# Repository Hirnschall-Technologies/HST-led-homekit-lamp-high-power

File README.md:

# High Power LED Lamp (HomeKit enabled, dimmable)
I designed this LED lighting system as a replacement for old halogen R7S uplights.      
These lamps often use high power (400W) bulbs outputing (according to the manufacturer) around 8800 lumen. Meanwhile the only off the shelf LED uplights I could find output 2000 lumen while using around 25W. Furthermore, altough replacement cob LEDs for R7S sockets are available they are typically "20W". I tested several of them and they started at around 15W, after around one hour they only used 10W, they are not bright enough, and they started flickering from time to time.

Also, I dislike how modern LED uplights have to be replaced entirely if a fault with the LEDs or dirver circuit occurs.
Using a modular design, we can reduce waste and wast less power.

### Features
- [x] High power Cree XHP50.3 LEDs (efficient, high CRI 90+) 
- [x] Modular design (2, 4, or 6 LEDs) 
- [x] Dimmable
- [x] Up to 108W, approx 12000 lumen
- [x] Homekit enabled (uses esp8266)
- [x] Manual On/Off switch in addition to Homekit (I use a 433MHz remote)
- [x] Uses 12V to 48V
- [x] Temperature sensor on each LED daughter board
- [x] Each LED on a separate daughter board, thus each led can be raplaced easily
- [x] Open source (Arduino compatible)

### References
The most useful resource for this project was SDG Electronics long-lasting video series on designing an LED ring-light for his microscope using the slightly older Cree XHP50.2 LEDs, as well as his modular LED driver board series.

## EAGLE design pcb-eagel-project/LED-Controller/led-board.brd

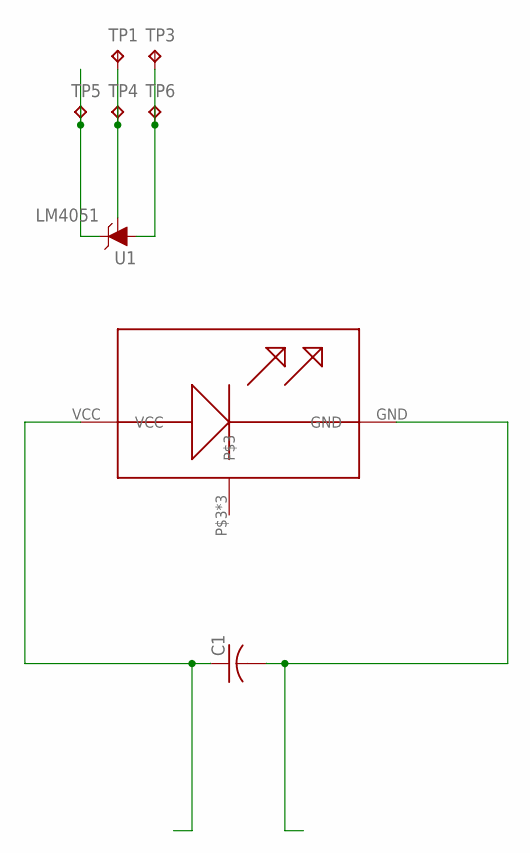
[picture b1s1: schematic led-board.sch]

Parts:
C1: C-USC0805; C0805
TP1, TP3, TP4, TP5, TP6: TPTP20SQ; TP20SQ
U1: LM4051; SOT23-3
U$3: XHP50.3

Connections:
unnamed: C1.1, U$3.VCC
unnamed: C1.2, U$3.GND
unnamed: TP1.TP, TP4.TP, U1.1 (ADJ)
unnamed: TP5.TP, U1.2 (C)
unnamed: TP3.TP, TP6.TP, U1.3 (A)

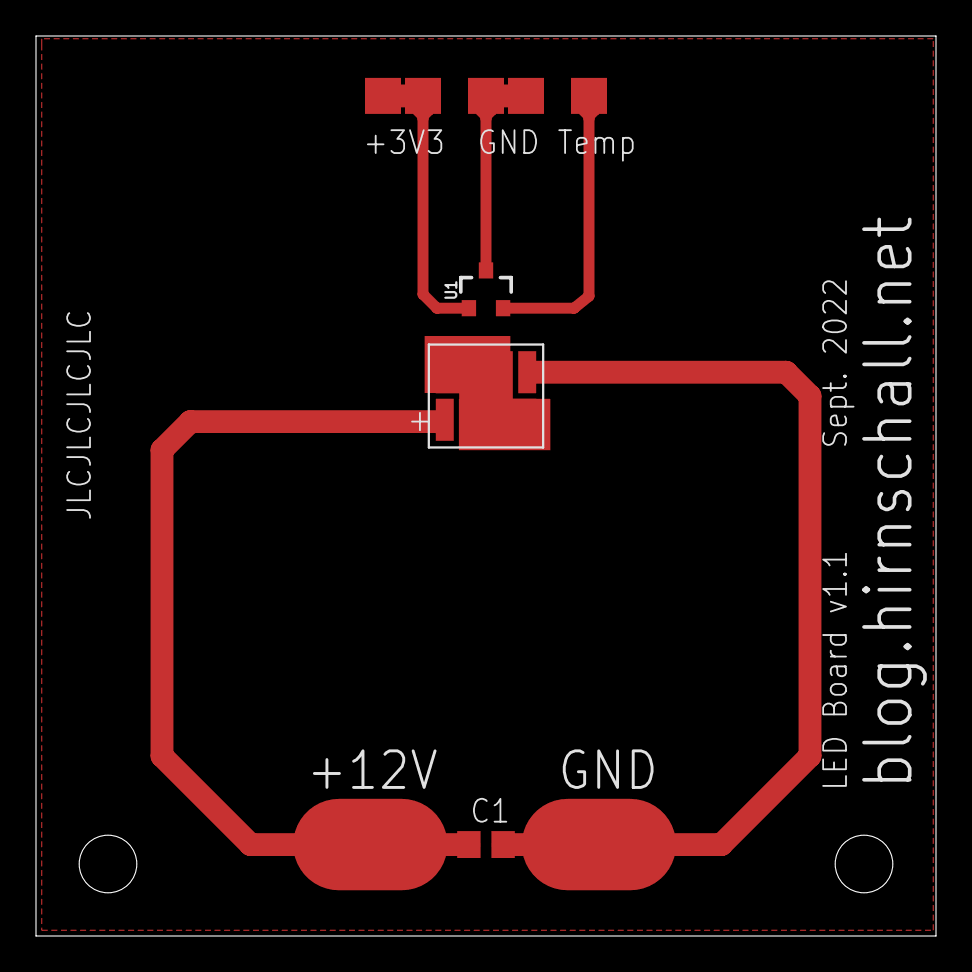
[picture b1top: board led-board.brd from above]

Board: 2 copper layers, 50.0 x 50.0 mm, 8 parts (0 on the bottom side), 5 nets.

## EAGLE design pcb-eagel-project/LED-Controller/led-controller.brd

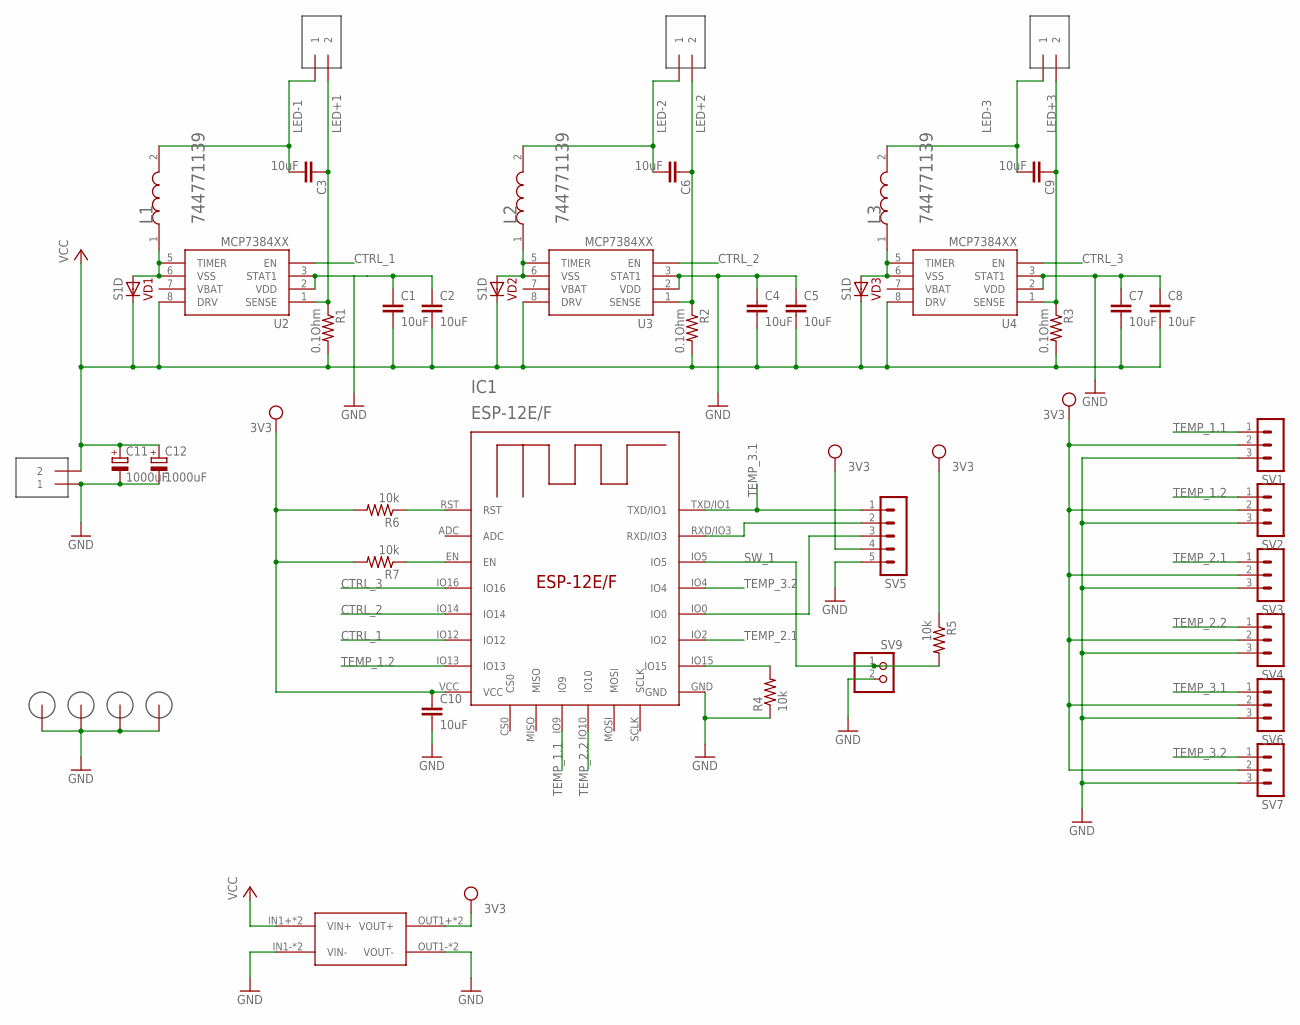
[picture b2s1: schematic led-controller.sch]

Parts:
C1, C2, C3, C4, C5, C6, C7, C8, C9, C10: 10uF; C0805K
C11, C12: 1000uF; E5-13
H1, H2, H3, H4: 3MM_HOLE
IC1: ESP-12E/F; ESP-12E
L1, L2, L3: 39uH; WURTH_ELECTRONICS_744771139_0
R1, R2, R3: 0.1Ohm; R1206
R4, R5, R6, R7: 10k; R0805
SV1, SV2, SV3, SV4, SV6, SV7: MA03-1
SV5: MA05-1
SV9: PINHD-1X2; 1X02
U2, U3, U4: MCP7384XX; MSOP8
U$3, U$5, U$7, U$8: TERMINAL_2P; KF301-2P
U$10: MP1584; DC-BRICK
VD1, VD2, VD3: S1D; DO214AC

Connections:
3V3: C10.1, IC1.VCC, R5.1, R6.2, R7.2, SV1.2, SV2.2, SV3.2, SV4.2, SV5.4, SV6.2, SV7.2, U$10.OUT1+ (VOUT+), U$10.OUT2+ (VOUT+)
CTRL_1: IC1.IO12, U2.4 (EN)
CTRL_2: IC1.IO14, U3.4 (EN)
CTRL_3: IC1.IO16, U4.4 (EN)
GND: C1.1, C2.1, C4.1, C5.1, C7.1, C8.1, C10.2, C11.-, C12.-, H1.P$1, H1.P$2, H1.P$3, H1.P$4, H1.P$5, H1.P$6, H1.P$7, H1.P$8, H1.P$9, H2.P$1, H2.P$2, H2.P$3, H2.P$4, H2.P$5, H2.P$6, H2.P$7, H2.P$8, H2.P$9, H3.P$1, H3.P$2, H3.P$3, H3.P$4, H3.P$5, H3.P$6, H3.P$7, H3.P$8, H3.P$9, H4.P$1, H4.P$2, H4.P$3, H4.P$4, H4.P$5, H4.P$6, H4.P$7, H4.P$8, H4.P$9, IC1.GND, R4.1, SV1.3, SV2.3, SV3.3, SV4.3, SV5.5, SV6.3, SV7.3, SV9.2, U2.2 (VDD), U2.3 (STAT1), U3.2 (VDD), U3.3 (STAT1), U4.2 (VDD), U4.3 (STAT1), U$8.1, U$10.IN1- (VIN-), U$10.IN2- (VIN-), U$10.OUT1- (VOUT-), U$10.OUT2- (VOUT-)
LED+1: C3.1, R1.1, U2.1 (SENSE), U$3.2
LED+2: C6.1, R2.1, U3.1 (SENSE), U$5.2
LED+3: C9.1, R3.1, U4.1 (SENSE), U$7.2
LED-1: C3.2, L1.2, U$3.1
LED-2: C6.2, L2.2, U$5.1
LED-3: C9.2, L3.2, U$7.1
unnamed: IC1.RST, R6.1
unnamed: IC1.EN, R7.1
unnamed: L2.1, U3.5 (TIMER), U3.6 (VSS), VD2.A
unnamed: L3.1, U4.5 (TIMER), U4.6 (VSS), VD3.A
unnamed: L1.1, U2.5 (TIMER), U2.6 (VSS), VD1.A
unnamed: IC1.IO15, R4.2
unnamed: IC1.IO0, SV5.3
unnamed: IC1.RXD/IO3, SV5.2
SW_1: IC1.IO5, R5.2, SV9.1
TEMP_1.1: IC1.IO9, SV1.1
TEMP_1.2: IC1.IO13, SV2.1
TEMP_2.1: IC1.IO2, SV3.1
TEMP_2.2: IC1.IO10, SV4.1
TEMP_3.1: IC1.TXD/IO1, SV5.1, SV6.1
TEMP_3.2: IC1.IO4, SV7.1
VCC: C1.2, C2.2, C4.2, C5.2, C7.2, C8.2, C11.+, C12.+, R1.2, R2.2, R3.2, U2.8 (DRV), U3.8 (DRV), U4.8 (DRV), U$8.2, U$10.IN1+ (VIN+), U$10.IN2+ (VIN+), VD1.C, VD2.C, VD3.C

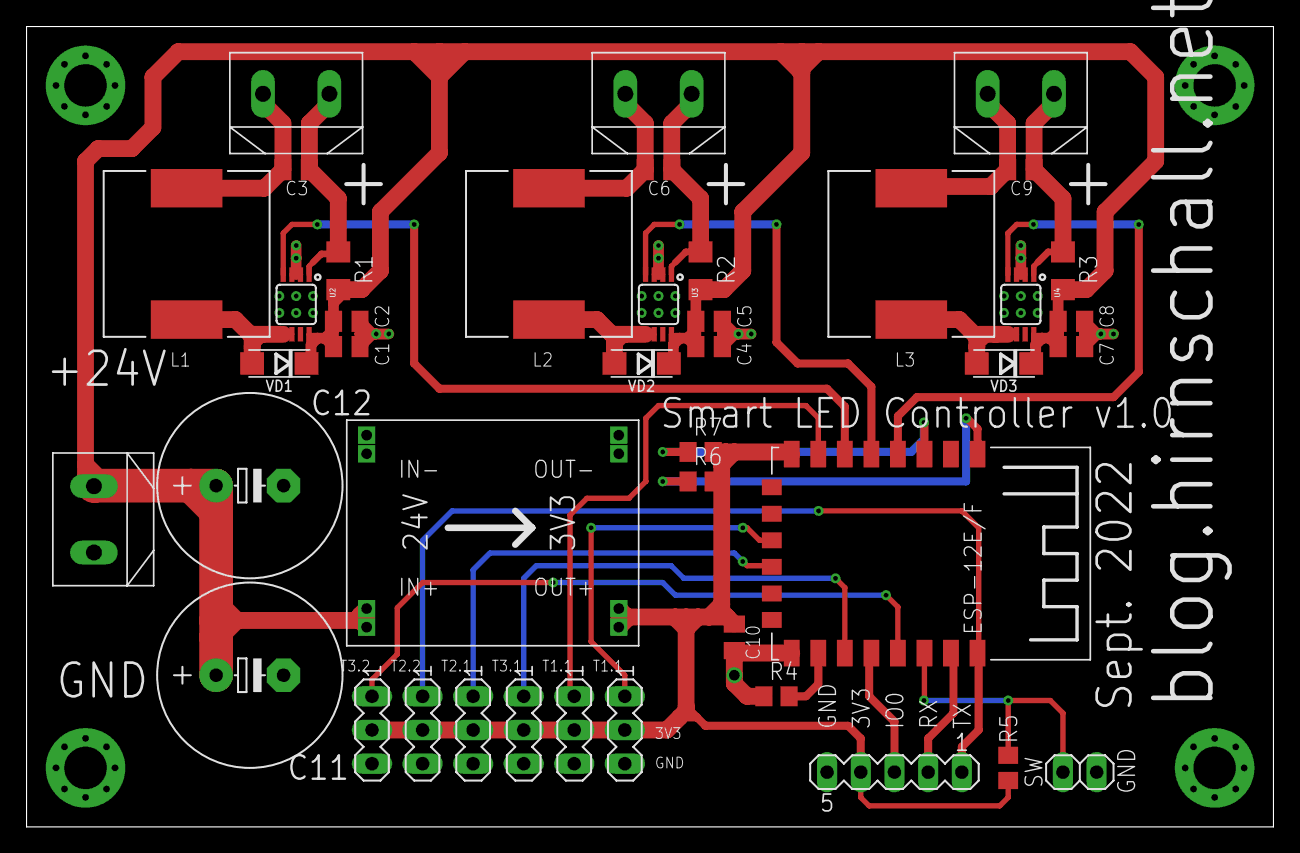
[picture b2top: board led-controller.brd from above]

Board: 2 copper layers, 94.0 x 60.3 mm, 46 parts (0 on the bottom side), 27 nets.

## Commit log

2022-10-09 first draft of an asymmetrical 6 led layout/mount for uplights
2022-10-10 add ed pcb source files - autodesk eagel project
2022-10-25 firmware

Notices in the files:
parts and their libraries:
SparkFun-DiscreteSemi: Licensing: Creative Commons ShareAlike 4.0 International - https://creativecommons.org/licenses/by-sa/4.0
